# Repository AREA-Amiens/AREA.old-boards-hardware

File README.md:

# AREA.old-boards-hardware
Hardware for AREA.old boards. Clone the repo on your local disk and with kicad you can modify the board or create new ones.

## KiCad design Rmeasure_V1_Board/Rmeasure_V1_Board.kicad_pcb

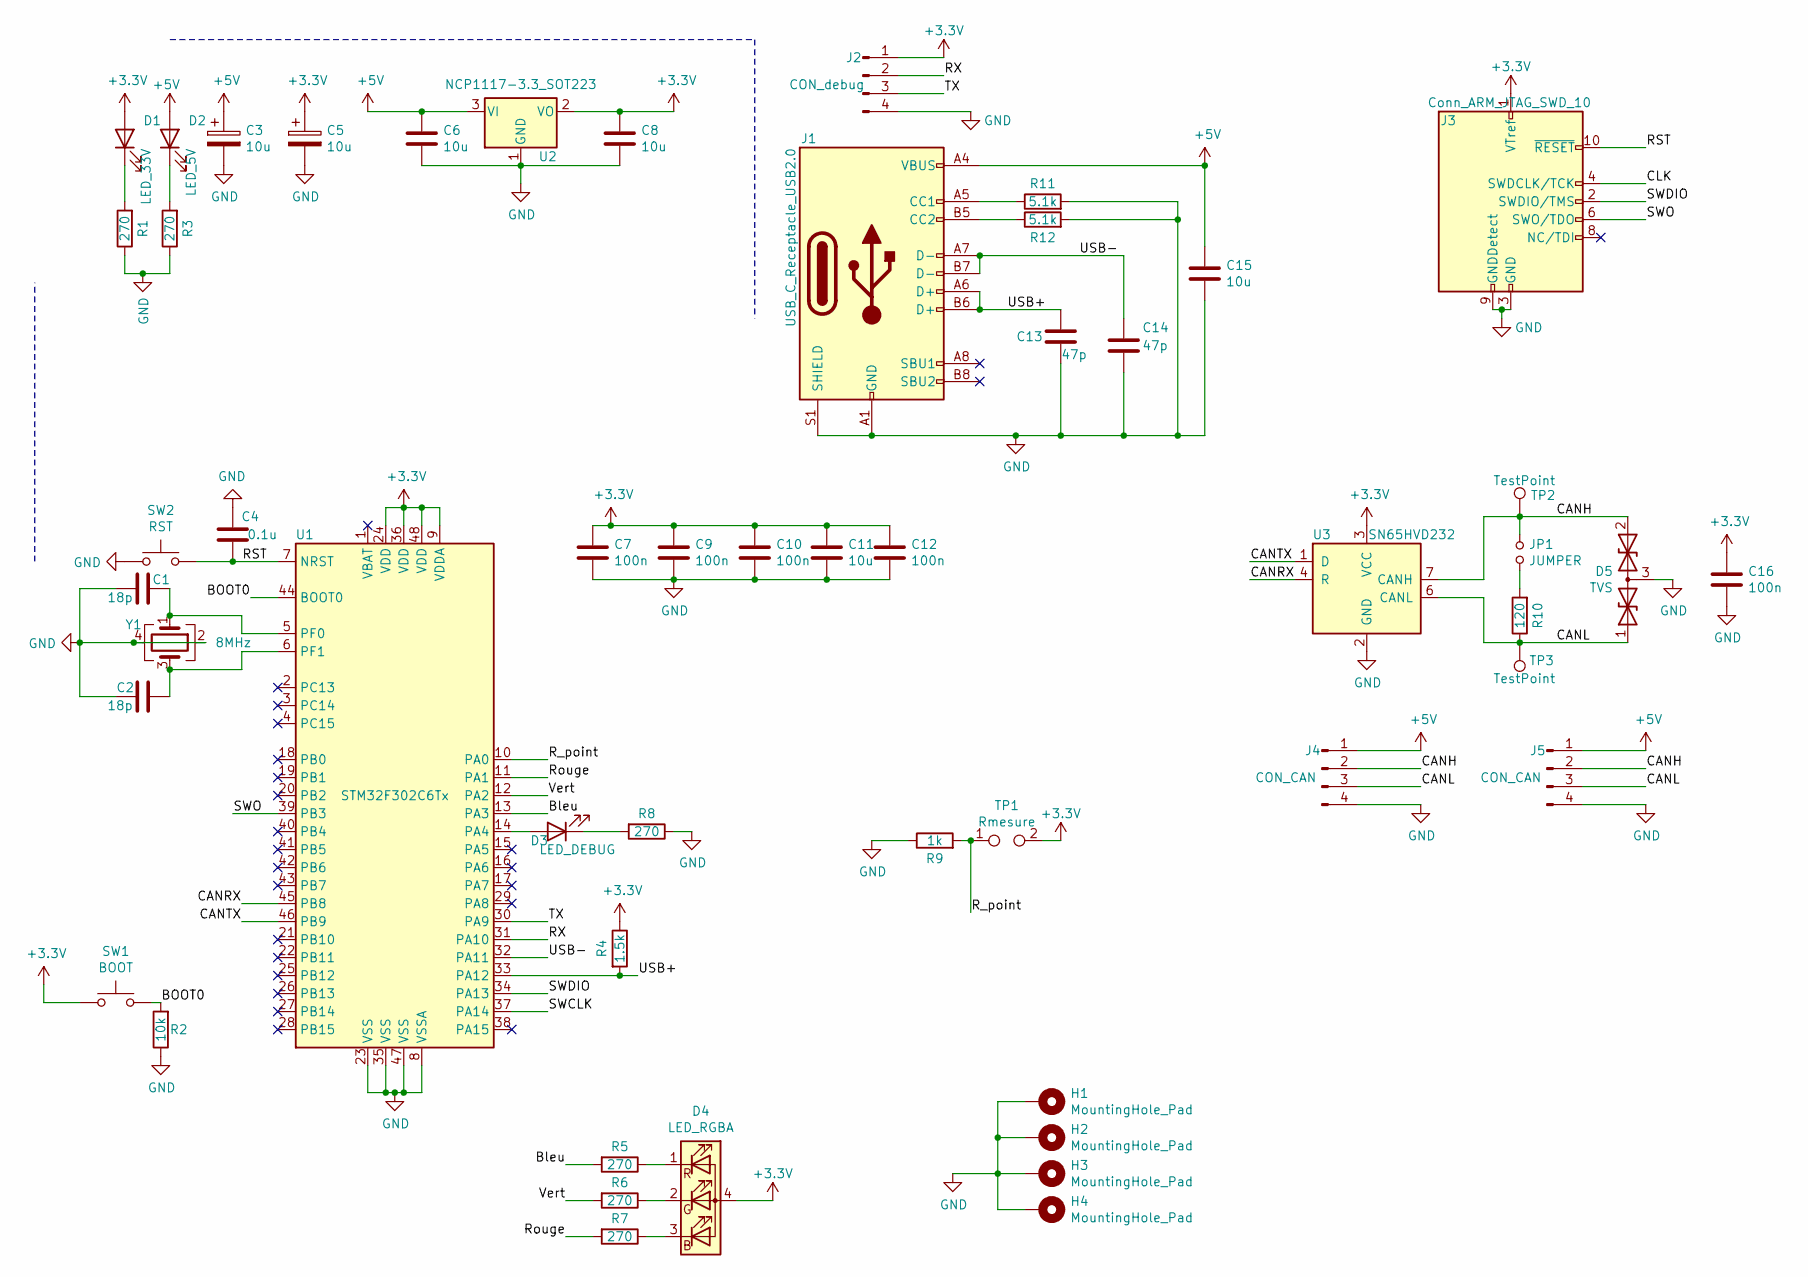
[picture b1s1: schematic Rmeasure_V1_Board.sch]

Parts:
C1, C2: 18p; C_0805_2012Metric_Pad1.18x1.45mm_HandSolder
C3, C5: 10u; CP_Radial_D4.0mm_P2.00mm
C4: 0.1u; C_0805_2012Metric
C6, C8, C11, C15: 10u; C_0805_2012Metric
C7, C9, C10, C12, C16: 100n; C_0805_2012Metric
C13, C14: 47p; C_0805_2012Metric
D1: LED_33V; LED_0805_2012Metric
D2: LED_5V; LED_0805_2012Metric
D3: LED_DEBUG; LED_0805_2012Metric
D4: LED_RGBA; LED_SK6812_EC15_1.5x1.5mm
D5: TVS; SOT-23
H1, H2, H3, H4: MountingHole_Pad; MountingHole_3.2mm_M3_Pad_Via
J1: USB_C_Receptacle_USB2.0; USB_C_Receptacle_GCT_USB4085
J2: CON_debug; Wuerth_2mm_4pin_62000411622
J3: Conn_ARM_JTAG_SWD_10; PinHeader_2x05_P1.27mm_Vertical
J4, J5: CON_CAN; Wuerth_2mm_4pin_62000411622
JP1: JUMPER; PinHeader_1x02_P2.54mm_Vertical
R1, R3, R5, R6, R7, R8: 270; R_0805_2012Metric
R2: 10k; R_0805_2012Metric
R4: 1.5k; R_0805_2012Metric
R9: 1k; R_0805_2012Metric
R10: 120; R_0805_2012Metric
R11, R12: 5.1k; R_0805_2012Metric
SW1: BOOT; SW_SPST_CK_RS282G05A3
SW2: RST; SW_SPST_CK_RS282G05A3
TP1: Rmesure; TestPoint_Pad_4.0x4.0mm
TP2, TP3: TestPoint; TestPoint_Loop_D1.80mm_Drill1.0mm_Beaded
U1: STM32F302C6Tx; LQFP-48_7x7mm_P0.5mm
U2: NCP1117-3.3_SOT223; SOT-223-3_TabPin2
U3: SN65HVD232; SOIC-8_3.9x4.9mm_P1.27mm
Y1: 8MHz; Crystal_SMD_5032-4Pin_5.0x3.2mm

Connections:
+5V: C3.1, C6.1, C15.1, D2.2 (A), J1.A4 (VBUS), J1.A9 (VBUS), J1.B4 (VBUS), J1.B9 (VBUS), J4.1, J5.1, U2.3 (VI)
/BOOT0: R2.2, SW1.2, U1.44 (BOOT0); also elsewhere on the board
/Bleu: R5.2, U1.13 (PA3)
/CANH: D5.2 (A2), J4.2, J5.2, JP1.1, TP2.1, U3.7 (CANH); also elsewhere on the board
/CANL: D5.1 (A1), J4.3, J5.3, R10.1, TP3.1, U3.6 (CANL)
/CANRX: U1.45 (PB8), U3.4 (R)
/CANTX: U1.46 (PB9), U3.1 (D)
/CLK: J3.4 (SWDCLK/TCK)
/RST: C4.1, J3.10 (~RESET~), SW2.2, U1.7 (NRST); also elsewhere on the board
/RX: J2.2, U1.31 (PA10)
/R_point: R9.2, TP1.1, U1.10 (PA0)
/Rouge: R7.2, U1.11 (PA1)
/SWCLK: U1.37 (PA14)
/SWDIO: J3.2 (SWDIO/TMS), U1.34 (PA13)
/SWO: J3.6 (SWO/TDO), U1.39 (PB3)
/TX: J2.3, U1.30 (PA9)
/USB+: C13.1, J1.A6 (D+), J1.B6 (D+), R4.2, U1.33 (PA12)
/USB-: C14.1, J1.A7 (D-), J1.B7 (D-), U1.32 (PA11)
/Vert: R6.2, U1.12 (PA2)
unnamed: C1.1, U1.5 (PF0), Y1.1
unnamed: C2.1, U1.6 (PF1), Y1.3
unnamed: D1.1 (K), R1.2
unnamed: D2.1 (K), R3.2
unnamed: D3.1 (K), R8.2
unnamed: D3.2 (A), U1.14 (PA4)
unnamed: D4.1 (RK), R5.1
unnamed: D4.2 (GK), R6.1
unnamed: D4.3 (BK), R7.1
unnamed: J1.A5 (CC1), R11.1
unnamed: J1.B5 (CC2), R12.1
unnamed 34: JP1.2, R10.2; also elsewhere on the board

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
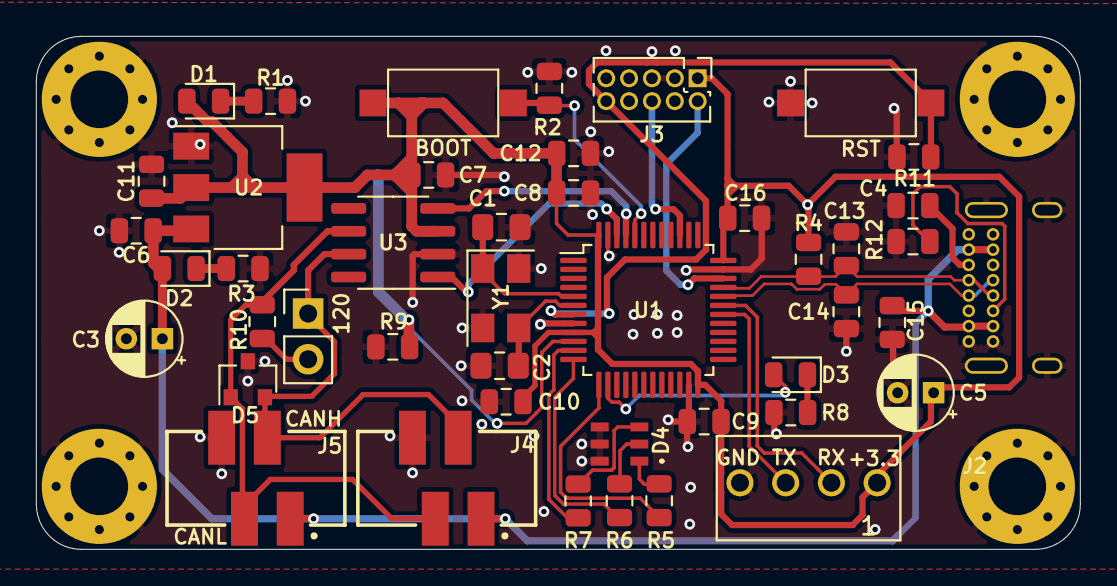
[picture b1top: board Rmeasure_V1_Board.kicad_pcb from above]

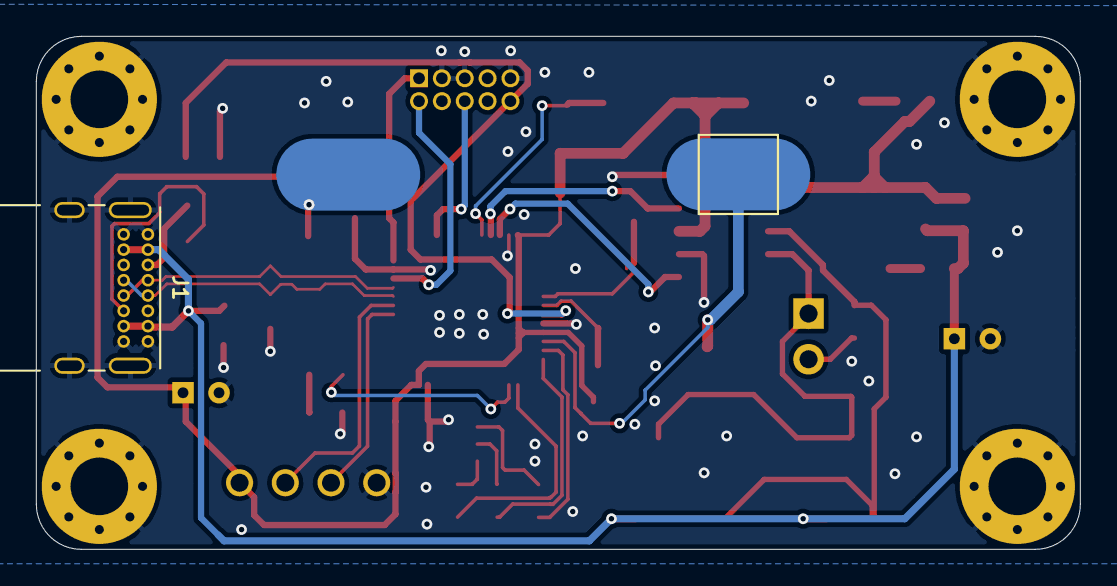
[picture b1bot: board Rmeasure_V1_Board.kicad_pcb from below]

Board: 2 copper layers, 58.0 x 28.5 mm, 50 parts (2 on the bottom side), 31 nets.

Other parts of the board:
120: JUMPER; PinHeader_1x02_P2.54mm_Vertical
BOOT: BOOT; SW_SPST_CK_RS282G05A3
RST: RST; SW_SPST_CK_RS282G05A3

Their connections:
/BOOT0: BOOT.2; also elsewhere on the board
/CANH: 120.1; also elsewhere on the board
/RST: RST.2; also elsewhere on the board
unnamed 34: 120.2; also elsewhere on the board

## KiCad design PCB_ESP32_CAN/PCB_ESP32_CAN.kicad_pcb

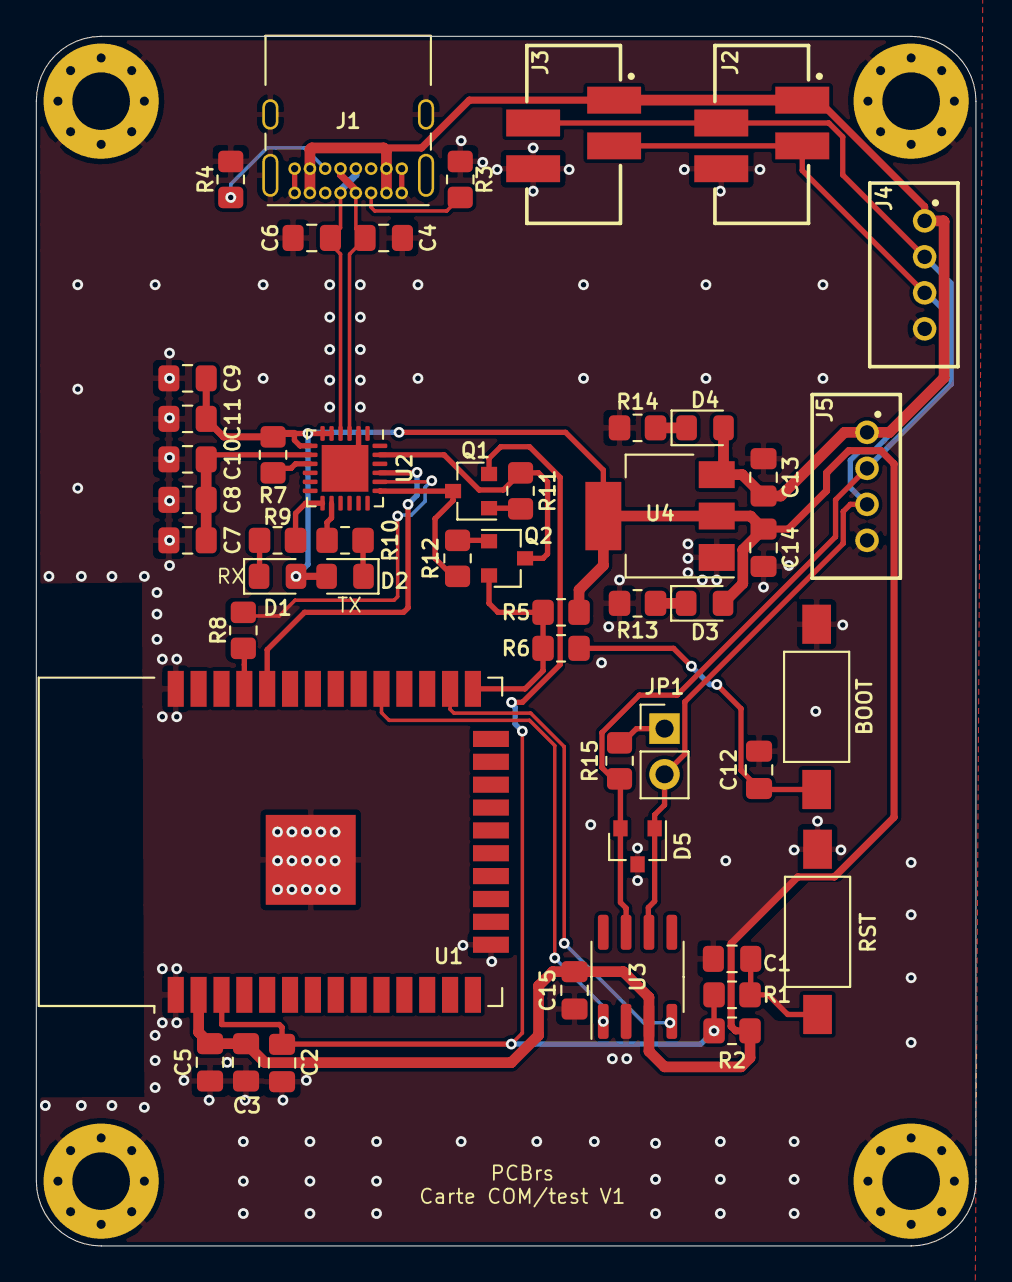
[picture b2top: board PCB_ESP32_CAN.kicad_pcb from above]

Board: 2 copper layers, 52.2 x 67.2 mm, 53 parts (0 on the bottom side), 30 nets.

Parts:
BOOT: BOOT; SW_SPST_FSMSM
C1, C2, C12: 1n; C_0805_2012Metric_Pad1.18x1.45mm_HandSolder
C3, C7, C8, C9, C13, C14: 10u; C_0805_2012Metric_Pad1.18x1.45mm_HandSolder
C4, C6: 47p; C_0805_2012Metric_Pad1.18x1.45mm_HandSolder
C5, C10, C11, C15: 100n; C_0805_2012Metric_Pad1.18x1.45mm_HandSolder
D1: LED_RX; LED_0805_2012Metric_Pad1.15x1.40mm_HandSolder
D2: LED_TX; LED_0805_2012Metric_Pad1.15x1.40mm_HandSolder
D3: LED_33V; LED_0805_2012Metric_Pad1.15x1.40mm_HandSolder
D4: LED_5V; LED_0805_2012Metric_Pad1.15x1.40mm_HandSolder
D5: TVS; SOT-23
H1, H2, H3, H4: M; MountingHole_3.2mm_M3_Pad_Via
J1: USB_C_Receptacle_USB2.0; USB_C_Receptacle_GCT_USB4085
J2, J3: CAN; 690367290476
J4, J5: CAN; Wuerth_2mm_4pin_62000411622
JP1: JUMP; PinHeader_1x02_P2.54mm_Vertical
Q1, Q2: Q_NPN_BCE; SOT-23
R1, R6, R14: 560; R_0805_2012Metric_Pad1.20x1.40mm_HandSolder
R2, R5, R7, R11, R12: 10K; R_0805_2012Metric_Pad1.20x1.40mm_HandSolder
R3, R4: 5.1K; R_0805_2012Metric_Pad1.20x1.40mm_HandSolder
R8: 470; R_0805_2012Metric_Pad1.20x1.40mm_HandSolder
R9, R13: 270; R_0805_2012Metric_Pad1.20x1.40mm_HandSolder
R10: 260; R_0805_2012Metric_Pad1.20x1.40mm_HandSolder
R15: 120; R_0805_2012Metric_Pad1.20x1.40mm_HandSolder
RST: RST; SW_SPST_FSMSM
U1: ESP32-WROOM-32
U2: CP2102N-A01-GQFN24; QFN-24-1EP_4x4mm_P0.5mm_EP2.6x2.6mm
U3: SN65HVD232; SOIC-8_3.9x4.9mm_P1.27mm
U4: NCP1117-3.3_SOT223; SOT-223-3_TabPin2

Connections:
+3V3: C3.1, C5.1, C9.1, C11.1, C14.1, C15.1, D1.2, D2.2, D3.2, R2.1, R5.1, R7.1, U1.2, U2.5, U2.6, U2.7, U3.3, U4.2
+5V: C7.1, C8.1, C10.1, C13.1, D4.2, J1.A4, J1.A9, J1.B4, J1.B9, J2.1, J3.1, J4.1, J5.1, U2.8, U4.3
/CANH: D5.2, J2.2, J3.2, J4.2, J5.2, R15.1, U3.7
/CANL: D5.1, J2.3, J3.3, J4.3, J5.3, JP1.2, U3.6
/DTR: Q2.3, R11.2, U2.23
/EN: C2.2, Q1.2, R1.1, R2.2, U1.3
/IO0: Q2.2, R5.2, R6.1, U1.25
/RTS: Q1.3, R12.2, U2.19
/RX: R8.1, U1.35
/RXCAN: U1.26, U3.4
/TX: U1.34, U2.21
/TXCAN: U1.29, U3.1
/USB+: C4.1, J1.A6, J1.B6, U2.3
/USB-: C6.1, J1.A7, J1.B7, U2.4
GND: BOOT.2, C1.2, C2.1, C3.2, C4.2, C5.2, C6.2, C7.2, C8.2, C9.2, C10.2, C11.2, C12.2, C13.2, C14.2, C15.2, D5.3, H1.1, H2.1, H3.1, H4.1, J1.A1, J1.A12, J1.B1, J1.B12, J1.S1, J2.4, J3.4, J4.4, J5.4, R3.1, R4.2, R13.2, R14.2, RST.2, U1.1, U1.15, U1.38, U1.39, U2.2, U2.25, U3.2, U4.1
unnamed: C1.1, R1.2, RST.1
unnamed: BOOT.1, C12.1, R6.2
unnamed: D1.1, R9.1
unnamed: D2.1, R10.1
unnamed: D3.1, R13.1
unnamed: D4.1, R14.1
unnamed: J1.A5, R3.2
unnamed: J1.B5, R4.1
unnamed: JP1.1, R15.2
unnamed: Q1.1, R11.1
unnamed: Q2.1, R12.1
unnamed: R7.2, U2.9
unnamed: R8.2, U2.20
unnamed: R9.2, U2.13
unnamed: R10.2, U2.14

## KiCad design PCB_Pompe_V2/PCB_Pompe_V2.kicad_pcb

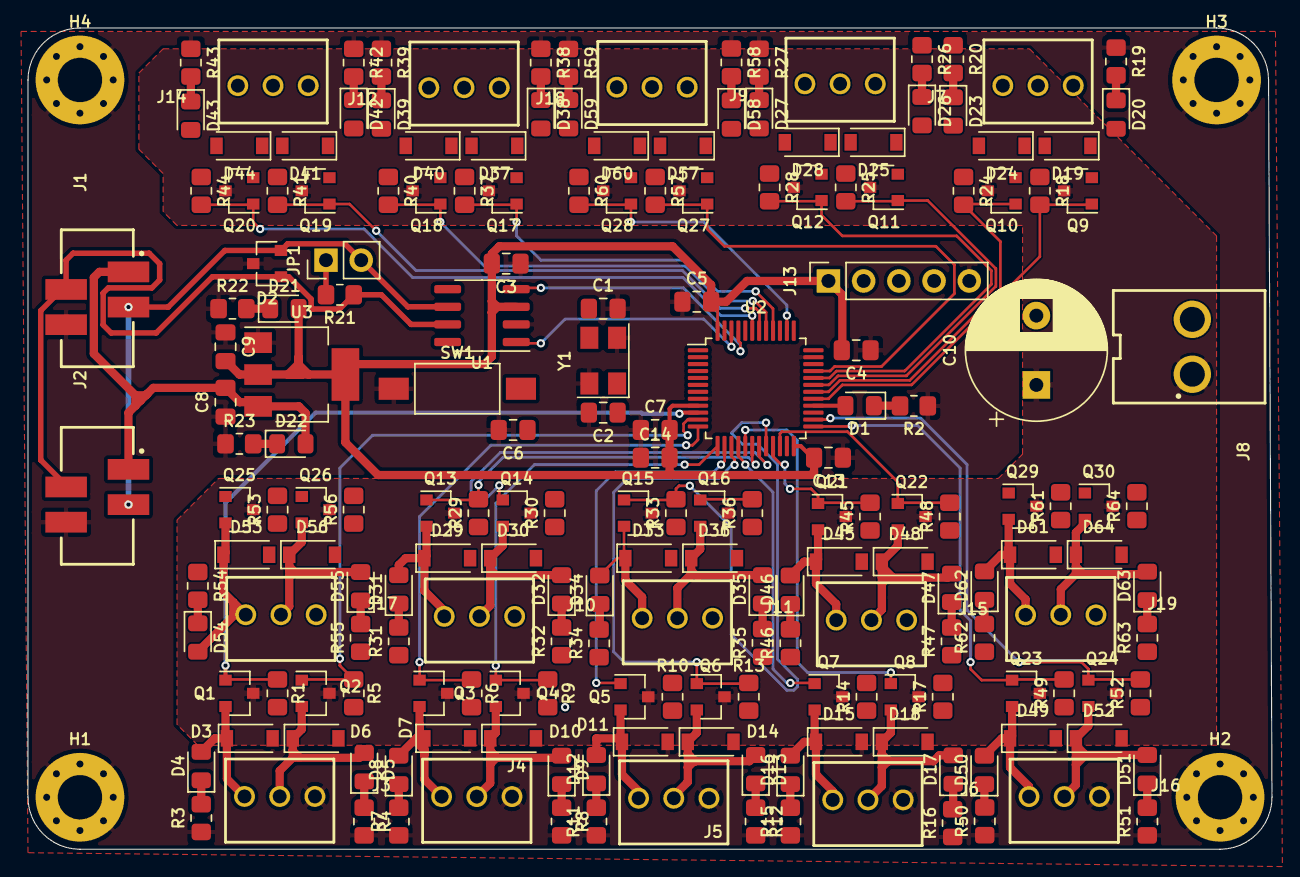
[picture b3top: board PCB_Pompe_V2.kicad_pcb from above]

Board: 4 copper layers, 89.8 x 59.2 mm, 199 parts (0 on the bottom side), 108 nets.

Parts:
C1, C2: 18pF; C_0805_2012Metric_Pad1.18x1.45mm_HandSolder
C3, C5, C7, C13, C14: 100nF; C_0805_2012Metric_Pad1.18x1.45mm_HandSolder
C4: 10µF; C_0805_2012Metric_Pad1.18x1.45mm_HandSolder
C6: 1u; C_0805_2012Metric_Pad1.18x1.45mm_HandSolder
C8, C9: 10u; C_0805_2012Metric_Pad1.18x1.45mm_HandSolder
C10: 470µF/50V; CP_Radial_D10.0mm_P5.00mm
D1, D4, D5, D8, D9, D12, D13, D16, D17, D20, D21, D22, D23, D26, D27, D31, D32, D34, D35, D38, D39, D42, D43, D46, D47, D50, D51, D54, D55, D58, D59, D62, D63: LED_DEBUG; LED_0805_2012Metric_Pad1.15x1.40mm_HandSolder
D2: D_TVS_x2_AAC; SOT-23
D3, D6, D7, D10, D11, D14, D15, D18, D19, D24, D25, D28, D29, D30, D33, D36, D37, D40, D41, D44, D45, D48, D49, D52, D53, D56, D57, D60, D61, D64: D; D_SOD-123
H1, H2, H3, H4: MountingHole_Pad; MountingHole_3.2mm_M3_Pad_Via
J1, J2: Conn_01x04_Female; 690367290476
J3, J4, J5, J6, J7, J9, J10, J11, J12, J14, J15, J16, J17, J18, J19: Conn_01x03_Female; Wuerth_2.54mm_3pins_61900311121
J8: Conn_01x02_Male; Wuerth_3.96mm_2pin_645002114822
J13: Conn_01x05_Female; PinSocket_1x05_P2.54mm_Vertical
JP1: Jumper_2_Open; PinHeader_1x02_P2.54mm_Vertical
Q1, Q2, Q3, Q4, Q5, Q6, Q7, Q8, Q9, Q10, Q11, Q12, Q13, Q14, Q15, Q16, Q17, Q18, Q19, Q20, Q21, Q22, Q23, Q24, Q25, Q26, Q27, Q28, Q29, Q30: DMN10H700S; SOT-23
R1, R5, R6, R9, R10, R13, R14, R17, R18, R24, R25, R28, R29, R30, R33, R36, R37, R40, R41, R44, R45, R48, R49, R52, R53, R56, R57, R60, R61, R64: 10k; R_0805_2012Metric_Pad1.20x1.40mm_HandSolder
R2, R22: 220; R_0805_2012Metric_Pad1.20x1.40mm_HandSolder
R3, R4, R7, R8, R11, R12, R15, R16, R19, R20, R23, R26, R27, R31, R32, R34, R35, R38, R39, R42, R43, R46, R47, R50, R51, R54, R55, R58, R59, R62, R63: 560; R_0805_2012Metric_Pad1.20x1.40mm_HandSolder
R21: 120; R_0805_2012Metric_Pad1.20x1.40mm_HandSolder
SW1: SW_Push; SW_SPST_FSMSM
U1: SN65HVD232; SOIC-8_3.9x4.9mm_P1.27mm
U2: STM32F302C6Tx; LQFP-48_7x7mm_P0.5mm
U3: NCP1117-3.3_SOT223; SOT-223-3_TabPin2
Y1: 8MHz; Crystal_SMD_5032-4Pin_5.0x3.2mm

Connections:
+3V3: C3.2, C4.2, C5.2, C7.2, C9.2, C13.2, C14.2, D21.2, J13.1, U1.3, U2.9, U2.24, U2.36, U2.48, U3.2
+5V: C8.2, D22.2, J1.1, J2.1, U3.3
+5VP: C10.1, J8.1, Q1.3, Q2.3, Q3.3, Q4.3, Q5.3, Q6.3, Q7.3, Q8.3, Q9.3, Q10.3, Q11.3, Q12.3, Q13.3, Q14.3, Q15.3, Q16.3, Q17.3, Q18.3, Q19.3, Q20.3, Q21.3, Q22.3, Q23.3, Q24.3, Q25.3, Q26.3, Q27.3, Q28.3, Q29.3, Q30.3
CANH: D2.1, J1.2, J2.2, R21.1, U1.7
CANL: D2.2, J1.3, J2.3, JP1.2, U1.6
GND: C1.2, C2.2, C3.1, C4.1, C5.1, C6.2, C7.1, C8.1, C9.1, C10.2, C13.1, C14.1, D2.3, D3.2, D6.2, D7.2, D10.2, D11.2, D14.2, D15.2, D18.2, D19.2, D24.2, D25.2, D28.2, D29.2, D30.2, D33.2, D36.2, D37.2, D40.2, D41.2, D44.2, D45.2, D48.2, D49.2, D52.2, D53.2, D56.2, D57.2, D60.2, D61.2, D64.2, H1.1, H2.1, H3.1, H4.1, J1.4, J2.4, J3.1, J4.1, J5.1, J6.1, J7.1, J8.2, J9.1, J10.1, J11.1, J12.1, J13.5, J14.1, J15.1, J16.1, J17.1, J18.1, J19.1, R1.1, R2.1, R3.1, R4.1, R5.1, R6.1, R7.1, R8.1, R9.1, R10.1, R11.1, R12.1, R13.1, R14.1, R15.1, R16.1, R17.1, R18.1, R19.1, R20.1, R22.1, R23.1, R24.1, R25.1, R26.1, R27.1, R28.1, R29.1, R30.1, R31.1, R32.1, R33.1, R34.1, R35.1, R36.1, R37.1, R38.1, R39.1, R40.1, R41.1, R42.1, R43.1, R44.1, R45.1, R46.1, R47.1, R48.1, R49.1, R50.1, R51.1, R52.1, R53.1, R54.1, R55.1, R56.1, R57.1, R58.1, R59.1, R60.1, R61.1, R62.1, R63.1, R64.1, SW1.1, U1.2, U2.8, U2.23, U2.35, U2.47, U3.1, Y1.2, Y1.4
unnamed: C1.1, U2.5, Y1.3
unnamed: C2.1, U2.6, Y1.1
unnamed: D1.1, R2.2
unnamed: D1.2, U2.28
unnamed: D4.1, R3.2
unnamed: D5.1, R4.2
unnamed: D8.1, R7.2
unnamed: D9.1, R8.2
unnamed: D12.1, R11.2
unnamed: D13.1, R12.2
unnamed: D16.1, R15.2
unnamed: D17.1, R16.2
unnamed: D20.1, R19.2
unnamed: D21.1, R22.2
unnamed: D22.1, R23.2
unnamed: D23.1, R20.2
unnamed: D26.1, R26.2
unnamed: D27.1, R27.2
unnamed: D31.1, R31.2
unnamed: D32.1, R32.2
unnamed: D34.1, R34.2
unnamed: D35.1, R35.2
unnamed: D38.1, R38.2
unnamed: D39.1, R39.2
unnamed: D42.1, R42.2
unnamed: D43.1, R43.2
unnamed: D46.1, R46.2
unnamed: D47.1, R47.2
unnamed: D50.1, R50.2
unnamed: D51.1, R51.2
unnamed: D54.1, R54.2
unnamed: D55.1, R55.2
unnamed: D58.1, R58.2
unnamed: D59.1, R59.2
unnamed: D62.1, R62.2
unnamed: D63.1, R63.2
unnamed: JP1.1, R21.2
OUT_P1: D3.1, D4.2, J3.3, Q1.2
OUT_P2: D7.1, D8.2, J4.3, Q3.2
OUT_P3: D11.1, D12.2, J5.3, Q5.2
OUT_P4: D15.1, D16.2, J6.3, Q7.2
OUT_P5: D19.1, D20.2, J7.3, Q9.2
OUT_P6: D25.1, D26.2, J9.3, Q11.2
OUT_P7: D29.1, D31.2, J10.3, Q13.2
OUT_P8: D33.1, D34.2, J11.3, Q15.2
OUT_P9: D37.1, D38.2, J12.3, Q17.2
OUT_P10: D41.1, D42.2, J14.3, Q19.2
OUT_P11: D45.1, D46.2, J15.3, Q21.2
OUT_P12: D49.1, D50.2, J16.3, Q23.2
OUT_P13: D53.1, D54.2, J17.3, Q25.2
OUT_P14: D57.1, D58.2, J18.3, Q27.2
OUT_P15: D61.1, D62.2, J19.3, Q29.2
OUT_V1: D5.2, D6.1, J3.2, Q2.2
OUT_V2: D9.2, D10.1, J4.2, Q4.2
OUT_V3: D13.2, D14.1, J5.2, Q6.2
OUT_V4: D17.2, D18.1, J6.2, Q8.2
OUT_V5: D23.2, D24.1, J7.2, Q10.2
OUT_V6: D27.2, D28.1, J9.2, Q12.2
OUT_V7: D30.1, D32.2, J10.2, Q14.2
OUT_V8: D35.2, D36.1, J11.2, Q16.2
OUT_V9: D39.2, D40.1, J12.2, Q18.2
OUT_V10: D43.2, D44.1, J14.2, Q20.2
OUT_V11: D47.2, D48.1, J15.2, Q22.2
OUT_V12: D51.2, D52.1, J16.2, Q24.2
OUT_V13: D55.2, D56.1, J17.2, Q26.2
OUT_V14: D59.2, D60.1, J18.2, Q28.2
OUT_V15: D63.2, D64.1, J19.2, Q30.2
P1: Q1.1, R1.2, U2.10
P2: Q3.1, R6.2, U2.12
P3: Q5.1, R10.2, U2.14
P4: Q7.1, R14.2, U2.16
P5: Q9.1, R18.2, U2.29
P6: Q11.1, R25.2, U2.31
P7: Q13.1, R29.2, U2.18
P8: Q15.1, R33.2, U2.20
P9: Q17.1, R37.2, U2.40
P10: Q19.1, R41.2, U2.42
P11: Q21.1, R45.2, U2.21
P12: Q23.1, R49.2, U2.25
P13: Q25.1, R53.2, U2.2
P14: Q27.1, R57.2, U2.33
P15: Q29.1, R61.2, U2.27
RST: C6.1, J13.2, SW1.2, U2.7
RXCAN: U1.4, U2.45
SWCLK: J13.3, U2.37
SWDIO: J13.4, U2.34
TXCAN: U1.1, U2.46
V1: Q2.1, R5.2, U2.11
V2: Q4.1, R9.2, U2.13
V3: Q6.1, R13.2, U2.15
V4: Q8.1, R17.2, U2.17
V5: Q10.1, R24.2, U2.30
V6: Q12.1, R28.2, U2.32
V7: Q14.1, R30.2, U2.19
V8: Q16.1, R36.2, U2.39
V9: Q18.1, R40.2, U2.41
V10: Q20.1, R44.2, U2.43
V11: Q22.1, R48.2, U2.22
V12: Q24.1, R52.2, U2.26
V13: Q26.1, R56.2, U2.3
V14: Q28.1, R60.2, U2.38
V15: Q30.1, R64.2, U2.4

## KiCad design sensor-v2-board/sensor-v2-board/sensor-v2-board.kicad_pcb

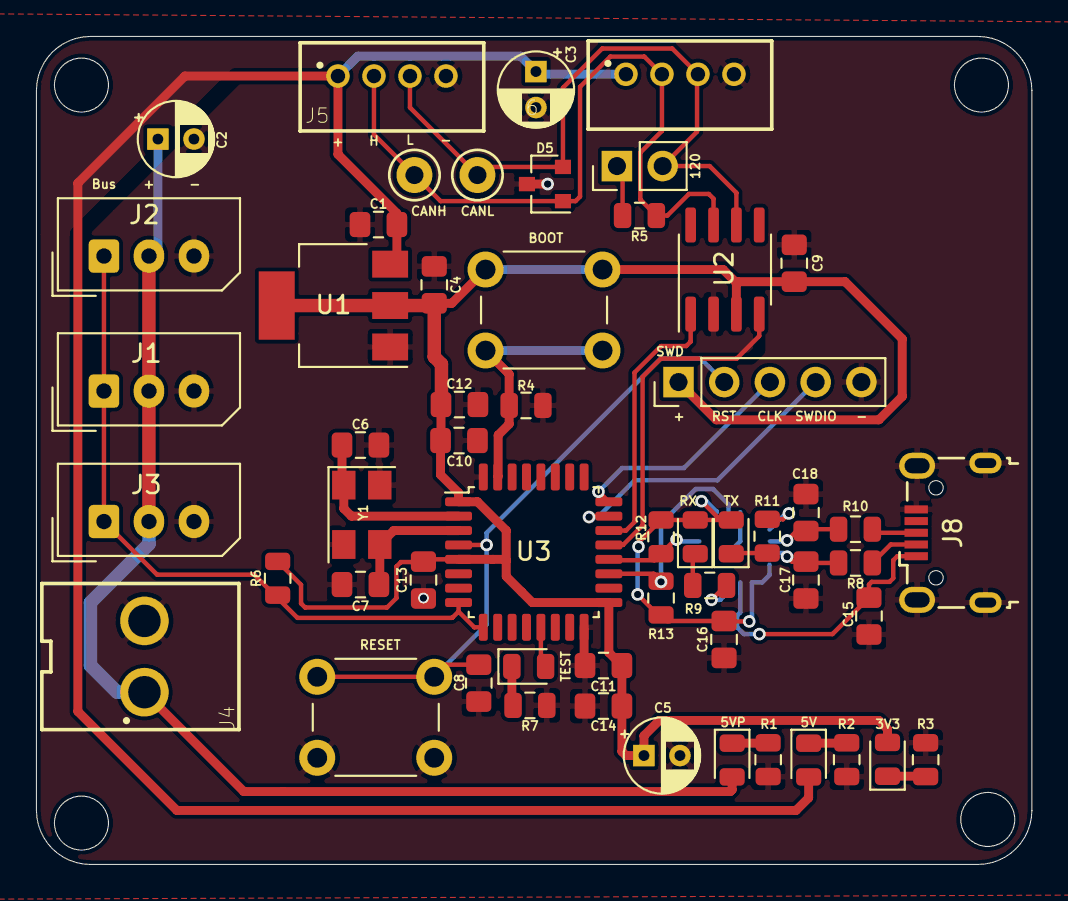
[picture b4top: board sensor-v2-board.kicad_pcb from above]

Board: 2 copper layers, 55.3 x 46.0 mm, 56 parts (1 on the bottom side), 33 nets.

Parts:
3V3, 5V, 5VP: 5vpLED; LED_0805_2012Metric
120: Jumper_2_Open; PinHeader_1x02_P2.54mm_Vertical
BOOT: Boot_Switch; SW_PUSH_6mm
C1, C4: 10µF; C_0805_2012Metric_Pad1.15x1.40mm_HandSolder
C2, C3, C5: 10µF; CP_Radial_D4.0mm_P2.00mm
C6, C7: 18pF; C_0805_2012Metric_Pad1.15x1.40mm_HandSolder
C8: 0.1µF; C_0805_2012Metric_Pad1.15x1.40mm_HandSolder
C9, C12, C13, C16: 100nF; C_0805_2012Metric_Pad1.15x1.40mm_HandSolder
C10, C11: 4.7µF; C_0805_2012Metric_Pad1.15x1.40mm_HandSolder
C14: 1µF; C_0805_2012Metric_Pad1.15x1.40mm_HandSolder
C15: 10nF; C_0805_2012Metric_Pad1.15x1.40mm_HandSolder
C17, C18: 47pF; C_0805_2012Metric_Pad1.15x1.40mm_HandSolder
CANH: TestPoint; TestPoint_Keystone_5000-5004_Miniature
CANL: TestPoint; TestPoint_Keystone_5000-5004_Miniature
D5: D_TVS_x2_AAC; SOT-23
J1, J2, J3: Conn_01x03_Male; Molex_SPOX_5267-03A_1x03_P2.50mm_Vertical
J4: Conn_01x02_Male; Wuerth_3.96mm_2pin_645002114822
J5, J6: Conn_01x04_Male; Wuerth_2mm_4pin_62000411622
J8: USB_B_Micro; USB_Micro-B_Wuerth_629105150521
R1, R2, R3, R7, R8, R9, R10, R11: 270; R_0805_2012Metric
R4, R12, R13: 10k; R_0805_2012Metric
R5: 120; R_0805_2012Metric
R6: 1.5k; R_0805_2012Metric
RESET: RST_Push; SW_PUSH_6mm
RX: RX_LED; LED_0805_2012Metric
SWD: Conn_01x05_Male; PinHeader_1x05_P2.54mm_Vertical
TEST: TST_LED; LED_0805_2012Metric
TX: TX_LED; LED_0805_2012Metric
U1: NCP1117-3.3_SOT223; SOT-223-3_TabPin2
U2: SN65HVD232; SOIC-8_3.9x4.9mm_P1.27mm
U3: STM32F042K6Tx; LQFP-32_7x7mm_P0.8mm
Ue: FT230XQ; QFN-16-1EP_4x4mm_P0.65mm_EP2.1x2.1mm
Y1: 8MHz; Crystal_SMD_5032-4Pin_5.0x3.2mm

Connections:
5VUSB: C15.1, J8.1, Ue.10
+3V3: 3V3.2, BOOT.1, C4.1, C5.1, C9.1, C10.1, C11.1, C12.1, C13.1, C14.1, R6.2, SWD.1, U1.2, U2.3, U3.1, U3.5, U3.17
+5V: 5V.2, C1.1, C3.1, J5.1, J6.1, U1.3
+5VP: 5VP.2, C2.1, J1.2, J2.2, J3.2, J4.1
CANH: CANH.1, D5.1, J5.2, J6.2, R5.1, U2.7
CANL: 120.2, CANL.1, D5.2, J5.3, J6.3, U2.6
CAN_RX: U2.4, U3.21
CAN_TX: U2.1, U3.22
GND: C1.2, C2.2, C3.2, C4.2, C5.2, C6.2, C7.2, C8.1, C9.2, C10.2, C11.2, C12.2, C13.2, C14.2, C15.2, C16.2, C17.2, C18.2, D5.3, J1.3, J2.3, J3.3, J4.2, J5.4, J6.4, J8.5, J8.6, R1.1, R2.1, R3.1, R4.1, R7.2, RESET.2, SWD.5, U1.1, U2.2, U3.16, U3.32, Ue.3, Ue.13, Ue.17, Y1.2, Y1.4
unnamed: C6.1, U3.2, Y1.1
unnamed: C7.1, U3.3, Y1.3
unnamed: C16.1, R12.2, R13.2, RX.2, TX.2, Ue.1, Ue.8, Ue.9
unnamed: 5VP.1, R1.2
unnamed: 5V.1, R2.2
unnamed: 3V3.1, R3.2
unnamed: R7.1, TEST.1
unnamed: TEST.2, U3.13
unnamed: R9.2, RX.1
unnamed: R11.1, TX.1
unnamed: 120.1, R5.2
unnamed: BOOT.2, R4.2, U3.31
unnamed: R9.1, Ue.11
unnamed: R11.2, Ue.5
RST: C8.2, RESET.1, SWD.2, U3.4
RXD: R13.1, U3.19, Ue.2
SERVO_BUS: J1.1, J2.1, J3.1, R6.1, U3.8, U3.9
SWDCLK: SWD.3, U3.24
SWDIO: SWD.4, U3.23
TXD: R12.1, U3.20, Ue.15
USB_DM: J8.2, R8.2
USB_DMo: C17.1, R8.1, Ue.7
USB_DP: J8.3, R10.2
USB_DPO: C18.1, R10.1, Ue.6

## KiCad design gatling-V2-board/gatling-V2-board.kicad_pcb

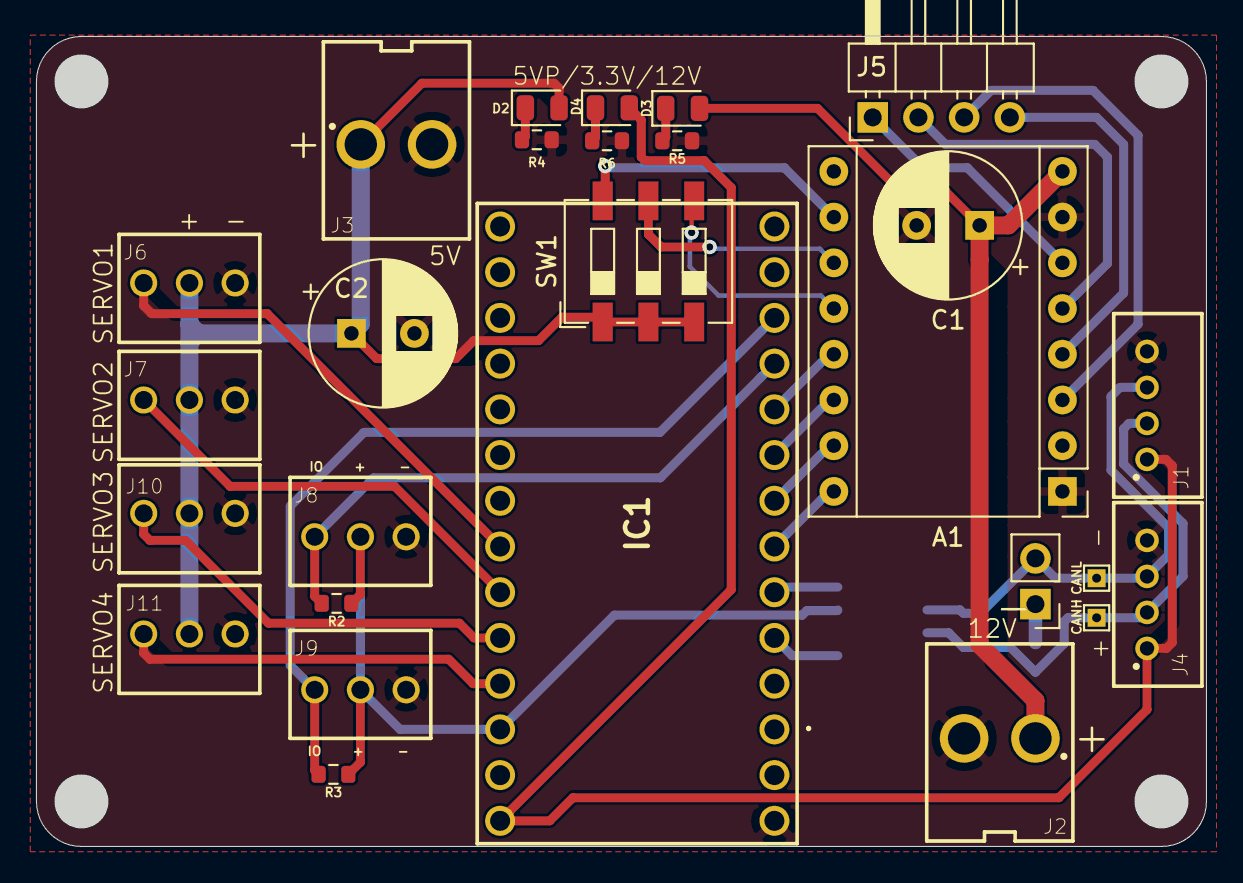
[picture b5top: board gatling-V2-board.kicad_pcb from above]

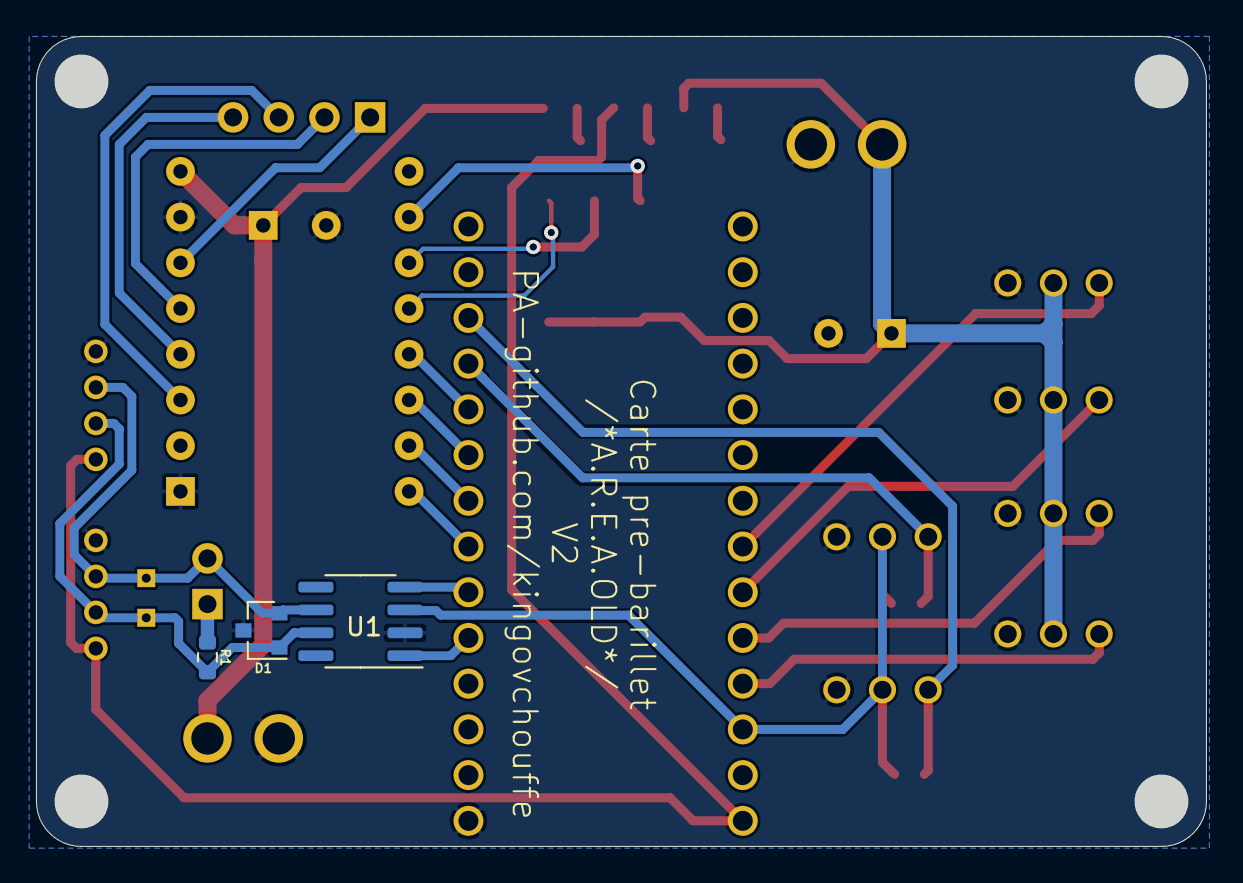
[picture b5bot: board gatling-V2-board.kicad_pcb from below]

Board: 2 copper layers, 65.0 x 45.0 mm, 30 parts (3 on the bottom side), 30 nets.

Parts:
A1: Pololu_Breakout_DRV8825; Pololu_Breakout-16_15.2x20.3mm
C1, C2: 100µF; CP_Radial_D8.0mm_P3.50mm
D1: D_TVS_x2_AAC; SOT-23
D2, D3, D4: LED; LED_0805_2012Metric
IC1: TEENSY3.2; TEENSY32
J1, J4: Conn_01x04_Male; Wuerth_2mm_4pin_62000411622
J2, J3: Conn_01x02_Male; Wuerth_3.96mm_2pin_645002114822
J5: Conn_01x04_Male; PinHeader_1x04_P2.54mm_Horizontal
J6, J7, J8, J9, J10, J11: Conn_01x03_Male; Wuerth_2.54mm_3pins_61900311121
JP1: Jumper; PinHeader_1x02_P2.54mm_Vertical
R1: 120; R_0603_1608Metric
R2, R3: 10K; R_0603_1608Metric
R4, R5, R6: 520; R_0603_1608Metric
SW1: SW_DIP_x03; SW_DIP_SPSTx03_Slide_6.7x9.18mm_W6.73mm_P2.54mm_LowProfile_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
TP1, TP2: TestPoint; TestPoint_THTPad_1.0x1.0mm_Drill0.5mm
U1: SN65HVD232; SOIC-8_3.9x4.9mm_P1.27mm

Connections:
+3V3: IC1.24, J8.2, J9.2, R2.1, R3.1, U1.3
+5V: D4.2, IC1.26, J1.1, J4.1
+5VP: C2.1, D2.2, J3.1, J6.2, J7.2, J10.2, J11.2, SW1.1, SW1.2, SW1.3
+12V: A1.8, C1.1, D3.2, J2.1
CANH: D1.1, J1.2, J4.2, R1.2, TP1.1, U1.7
CANL: D1.2, J1.3, J4.3, JP1.2, TP2.1, U1.6
CAN_RX: IC1.4, U1.4
CAN_TX: IC1.3, U1.1
DIR: A1.16, IC1.5
FOURCHE1: IC1.9, J8.1, R2.2
FOURCHE2: IC1.10, J9.1, R3.2
GND: A1.1, A1.7, C1.2, C2.2, D1.3, IC1.36, J1.4, J2.2, J3.2, J4.4, J6.1, J7.1, J8.3, J9.3, J10.1, J11.1, R4.2, R5.2, R6.2, U1.2
unnamed: A1.3, J5.3
unnamed: A1.4, J5.4
unnamed: A1.5, J5.2
unnamed: A1.6, J5.1
unnamed: A1.10, SW1.6
unnamed: A1.11, SW1.5
unnamed: A1.12, SW1.4
unnamed: D2.1, R4.1
unnamed: D3.1, R5.1
unnamed: D4.1, R6.1
unnamed: JP1.1, R1.1
RST: A1.13, IC1.8
SERVO1: IC1.20, J6.3
SERVO2: IC1.21, J7.3
SERVO3: IC1.22, J10.3
SERVO4: IC1.23, J11.3
SLP: A1.14, IC1.7
STEP: A1.15, IC1.6

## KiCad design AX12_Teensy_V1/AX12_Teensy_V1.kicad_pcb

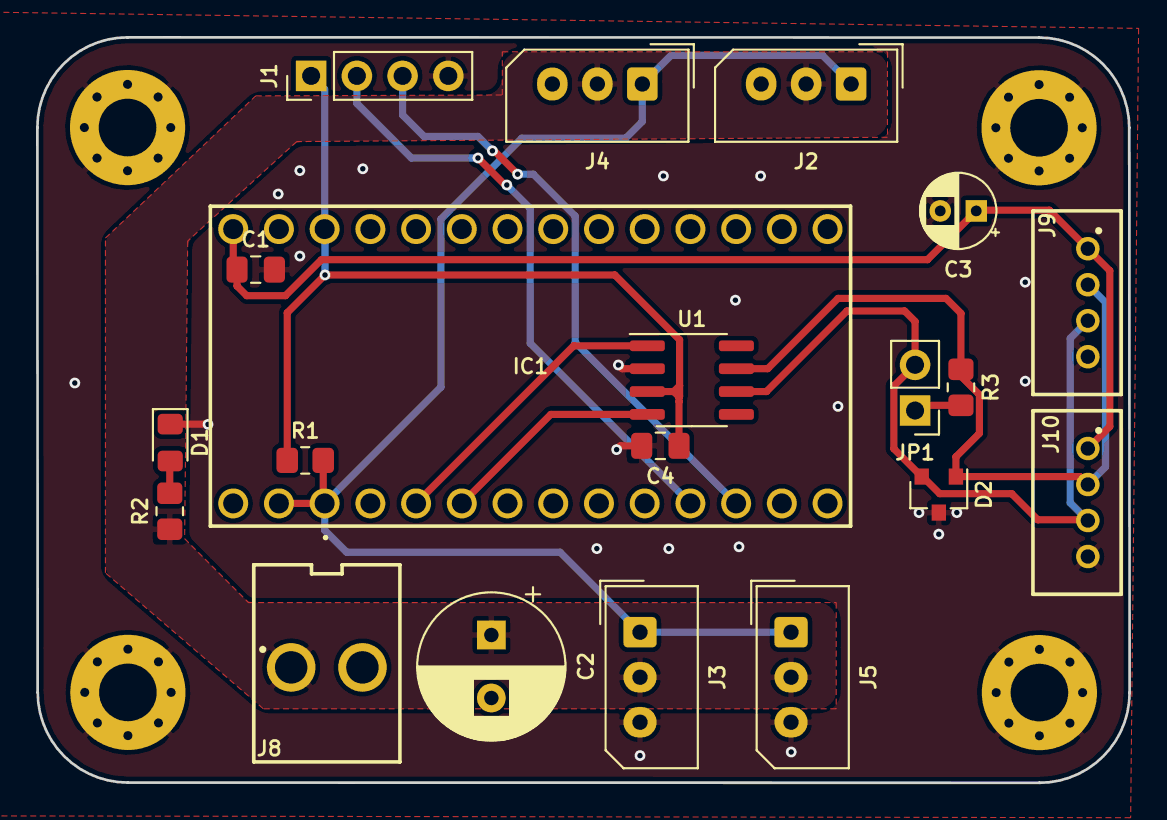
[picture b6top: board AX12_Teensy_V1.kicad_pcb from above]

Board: 2 copper layers, 60.7 x 41.4 mm, 24 parts (0 on the bottom side), 13 nets.

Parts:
C1, C4: 100n; C_0805_2012Metric_Pad1.18x1.45mm_HandSolder
C2: 100u; CP_Radial_D8.0mm_P3.50mm
C3: 10u; CP_Radial_D4.0mm_P2.00mm
D1: LED_12V; LED_0805_2012Metric_Pad1.15x1.40mm_HandSolder
D2: TVS; SOT-23
H1, H2, H3, H4: MountingHole_Pad; MountingHole_3.2mm_M3_Pad_Via
IC1: TEENSY3.2; TEENSY32
J1: uart; PinHeader_1x04_P2.54mm_Vertical
J2, J3, J4, J5: AX12; Molex_SPOX_5267-03A_1x03_P2.50mm_Vertical
J8: 12VP; Wuerth_3.96mm_2pin_645002114822
J9, J10: Conn_CAN; Wuerth_2mm_4pin_62000411622
JP1: 120; PinHeader_1x02_P2.54mm_Vertical
R1: 1.5K; R_0805_2012Metric_Pad1.20x1.40mm_HandSolder
R2: 2k; R_0805_2012Metric_Pad1.20x1.40mm_HandSolder
R3: 120; R_0805_2012Metric_Pad1.20x1.40mm_HandSolder
U1: SN65HVD232; SOIC-8_3.9x4.9mm_P1.27mm

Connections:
+3V3: C4.1, IC1.24, J1.1, R1.1, U1.3
+5V: C1.1, C3.1, IC1.26, J9.1, J10.1
+12V: C2.1, J2.2, J3.2, J4.2, J5.2, J8.1, R2.1
/AX12_BUS: IC1.1, IC1.37, J2.1, J3.1, J4.1, J5.1, R1.2
/CANH: D2.1, J9.2, J10.2, R3.1, U1.7
/CANL: D2.2, J9.3, J10.3, JP1.2, U1.6
/CANRX: IC1.4, U1.4
/CANTX: IC1.3, U1.1
/RX: IC1.10, J1.3
/TX: IC1.9, J1.2
GND: C1.2, C2.2, C3.2, C4.2, D1.1, D2.3, H1.1, H2.1, H3.1, H4.1, J1.4, J2.3, J3.3, J4.3, J5.3, J8.2, J9.4, J10.4, U1.2
unnamed: D1.2, R2.2
unnamed: JP1.1, R3.2
